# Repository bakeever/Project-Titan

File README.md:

# Project TITAN - Configurations Hyperion & Theia

**Developed by Bryce Keever and Benjamin Costello**  
ENGR 385 - Integration 2 | Spring 2025  
Colorado Mesa University  

## Overview

Project TITAN is an advanced autonomous rover designed and developed to demonstrate integrated engineering concepts, including mechatronics, software development, and system integration. This project is part of the ENGR 385 - Integration 2 course at Colorado Mesa University. It serves as a comprehensive exploration of practical engineering applications, combining modern hardware, software, and design methodologies to create a fully functional autonomous system.

Each rover utilizes two Arduino MEGA microcontrollers:
- **Rover Control Unit:** Manages autonomous navigation, sensor integration, and decision-making.
- **Handheld Control Console:** Provides manual control and telemetry monitoring capabilities.

### Features
- **Arduino Programming:** Custom code for sensor input, motor control, and communication protocols.
- **Mechanical Design:** A SolidWorks assembly for the rover chassis and components.
- **Human Interface:** A handheld console for monitoring and operation, including live sensor data visualization.
- **Obstacle Detection:** Utilizes HC-SR04 ultrasonic distance sensors for obstacle detection and avoidance.
- **Precise Movement:** Driven by precision-controlled motors.
- **Control Console:** An intuitive handheld device for manual operation and telemetry feedback.

By leveraging a multidisciplinary approach, Project TITAN demonstrates the practical integration of hardware design, embedded systems, and control strategies, providing a scalable foundation for future autonomous systems research and development.

## Bill of Materials - Hyperion (Tank Rover)
| **Component**          | **Description**                                        | **Quantity** |
|-------------------------|--------------------------------------------------------|--------------|
| Arduino MEGA           | Microcontroller for the rover brain                   | 1            |
| Arduino MEGA           | Microcontroller for the handheld control console      | 1            |
| Wiring Kit             | Wiring for connections                                | Various      |
| HC-SR04 Ultrasonic Sensors | Ultrasonic distance sensors for obstacle detection | 3          |
| Motors                 | Motors for rover movement                             | TBD          |
| Power Supply           | 5V DC battery pack                                    | 1            |
| Chassis Components     | Mechanical parts for rover structure                  | TBD          |
| Wheels/Tracks          | Mobility components                                   | TBD          |
| Miscellaneous          | Other components and accessories                      | TBD          |

## Bill of Materials - Theia (4x4 Rover)
| **Component**          | **Description**                                        | **Quantity** |
|-------------------------|--------------------------------------------------------|--------------|
| Arduino MEGA           | Microcontroller for the rover brain                   | 1            |
| Arduino MEGA           | Microcontroller for the handheld control console      | 1            |
| Wiring Kit             | Wiring for connections                                | Various      |
| HC-SR04 Ultrasonic Sensors | Ultrasonic distance sensors for obstacle detection | 3          |
| Motors                 | Motors for rover movement                             | TBD          |
| Power Supply           | 5V DC battery pack                                    | 1            |
| Chassis Components     | Mechanical parts for rover structure                  | TBD          |
| Wheels/Tracks          | Mobility components                                   | TBD          |
| Miscellaneous          | Other components and accessories                      | TBD          |

## Website Link
https://org.coloradomesa.edu/~bakeever/

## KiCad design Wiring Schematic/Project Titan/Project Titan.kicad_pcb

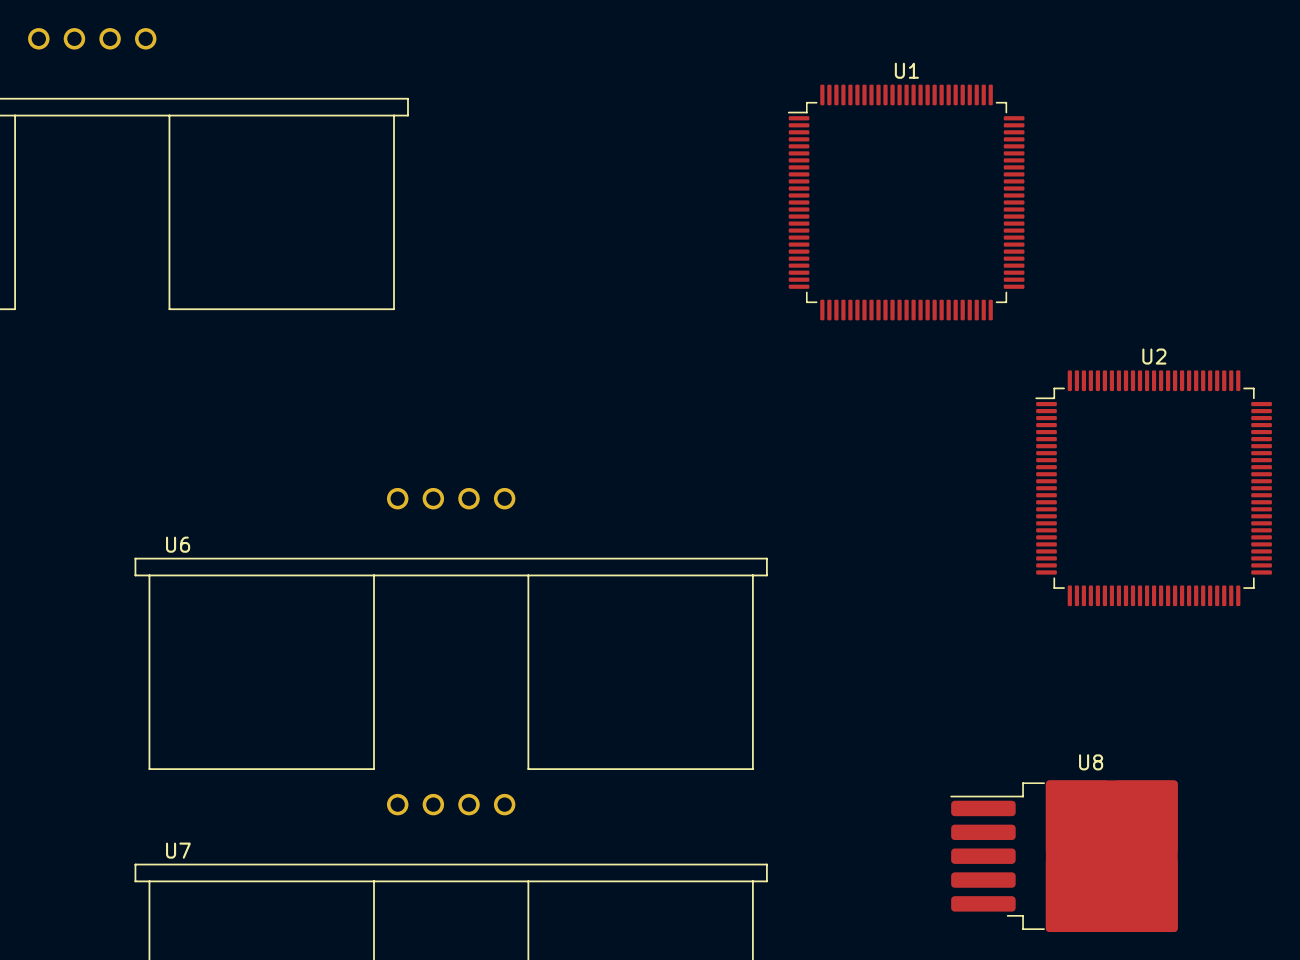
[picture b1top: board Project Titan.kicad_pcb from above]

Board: 2 copper layers, 6 parts (0 on the bottom side), 4 nets, no tracks yet.

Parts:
U1, U2: ATmega2560-16A; TQFP-100_14x14mm_P0.5mm
U3, U6, U7: HC-SR04; XCVR_HC-SR04
U8: LM2596S-ADJ; TO-263-5_TabPin3

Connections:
unnamed: U1.11 (GND), U1.32 (GND), U1.62 (GND), U1.81 (GND), U1.99 (GND)
unnamed: U1.10 (VCC), U1.31 (VCC), U1.61 (VCC), U1.80 (VCC)
unnamed: U2.11 (GND), U2.32 (GND), U2.62 (GND), U2.81 (GND), U2.99 (GND)
unnamed: U2.10 (VCC), U2.31 (VCC), U2.61 (VCC), U2.80 (VCC)

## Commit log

2025-01-31 Initial Website Push
2025-01-31 Website Functionality Update
2025-02-02 Project Update
2025-02-03 Update
    Should be all basic framework for website. Just needs to be populated with images and documents.
2025-02-04 Added CAD directory
2025-02-04 CAD update
    -Enlarged Idler shaft diameter to allow for free rotation on shaft.
    -added Servo, battery
2025-02-04 End of evening push
2025-02-05 Updated chassis. Assembly is left broken
2025-02-05 Wiring Structure Update
2025-02-05 Floating Assembly with all major components. Shows what Hyperion could look like
2025-02-05 No real changes
2025-02-07 Frame 1 update
2025-02-08 Beta assembly with STPs
2025-02-10 Wiring Update
2025-02-11 New Chassis
2025-02-11 Update README.md
    Website Link Fix & Added BOM Changes
2025-02-12 Added logo
2025-02-12 Logo update
2025-02-12 Logo fix #2
2025-02-12 Added screen.stp for console
2025-02-12 near completion on chaassis base
2025-02-14 Base STP ready
2025-02-14 Added mounting points on chassis base for the top half to be attached
2025-02-15 added first componenet of tensioner
2025-02-16 Added base for tread tensioner
2025-02-17 Tensioner almost ready
2025-02-18 Rails are designed and exported as stps
2025-02-22 Tensioner
2025-02-23 Buck booster mount STP added
2025-02-24 Created First pieces for payload dropping system.
2025-02-24 Create WIP_IN_CLASS_WORKING_CODE
2025-02-24 Create WIP_IN_CLASS_CODE
2025-02-26 Fixed broken assembly joints
2025-02-28 Door Assembly 80%
2025-02-28 Door Extras
2025-03-01 Block pooper V1
2025-03-01 Minor door update
2025-03-03 Code Update
2025-03-03 In Class Update
2025-03-03 finr tuning mission 1
2025-03-04 SolidWorks Assembly created
2025-03-04 Website Update for Grading #2
2025-03-05 Current Working Code
2025-03-05 In Class Testing
2025-03-05 Mission 1 succesful perameters
    - Rover changes speed after it's run for a while. the motor controllers heat up, giving extra juice. Need magnometers or encoders to verify correct feeds and speeds
2025-03-10 Added dimensioned drawing
2025-03-10 Dimensioned drawing adjustment
2025-03-12 second chassis adjustments
2025-03-14 Added ADXL345 tutorial page
2025-03-24 Schematic Update
2025-03-24 Magnometer code
2025-03-24 Sensor models are built
2025-03-24 Magnometer cradle
2025-03-24 cradle pt.2
2025-03-24 Mission 2B
2025-03-24 Added sin correction to avoid negative values
2025-03-24 Class Update
2025-03-24 exported Buck Converter
2025-03-26 Mission 2A nearly functional code
2025-04-02 Testing Update
2025-04-02 Fixed compass module
    cleaned up code structure, added correct compass navigation
2025-04-02 Mission 3_V1
2025-04-02 more conservative motor speed M3
2025-04-02 error Tank V2
2025-04-02 Fixed function bracket error
2025-04-07 Mission 3 functional!
2025-04-08 Control Center V.1 Update
2025-04-09 New Version of Tank Code
2025-04-14 Freecad -> Solidworks Migration
2025-04-16 In Class Fudge
2025-04-17 In Class WIP
2025-04-21 Blender model
2025-04-21 old changes
2025-04-22 Tank lid
2025-04-22 Update: Code Structure Revision
    Changed the motor variable declarations.
    Attempted to standardized function descriptions.
2025-04-23 CAD update
2025-04-24 Full SOLIDWORKS Model for upload
2025-04-30 Controller Update
2025-05-05 mission 4b debug
2025-05-07 Update Project_Titan_Tank_V3.ino
    Implement Mission 4B - RF waypoint navigation and return with GPS
    - Modified `mission_42()` function to support full waypoint mission behavior
    - Parses RF-transmitted GPS waypoint in format: "N09495W58784"
    - Constructs target GPS coordinates from 12-char message
    - Waits for valid GPS fix before executing motion
    - Saves current location as start point before traveling
2025-05-07 Update Project_Titan_Tank_V3.ino
    - Enhanced driveTowardsTarget() to detect and avoid obstacles using ultrasonic sensors
    - Uses TRIG_PIN_LEFT / RIGHT and ECHO_PIN_LEFT / RIGHT to measure distance
    - Performs U-turn if obstacle detected ahead (both sensors < 300mm)
    - Performs side-step (left/right) if obstacle is detected on one side
    - Reorients after avoidance and resumes GPS navigation
    - Keeps mission_41 and mission_42 logic unchanged by embedding avoidance in steering
2025-05-13 Presentation Update 1
2025-05-14 Website mission 4 update
